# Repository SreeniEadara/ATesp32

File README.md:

# ATesp32

This is an ATmega32A replacement that uses the ESP32-S3.
Why? Because I bought ATmega32-based keyboard PCBs (the Discipline), love it and want to add wireless capabilities (BLE) and native USB.

I've made efforts to maintain the same number of GPIO, but there will be many differences you would encounter if trying to use this as an ATmega32A replacement. These would include logic levels, availability of analog pins, clock, etc.

Thank you to Adafruit for making the Feather and QtPy boards for the ESP32-S3!
I heavily referenced these in this design.
https://github.com/adafruit/Adafruit-Feather-ESP32-S3-PCB
https://github.com/adafruit/Adafruit-QT-Py-ESP32-S3-PCB/tree/main

Call me an Adafruit shill if you will, but you can support open hardware by purchasing from them.

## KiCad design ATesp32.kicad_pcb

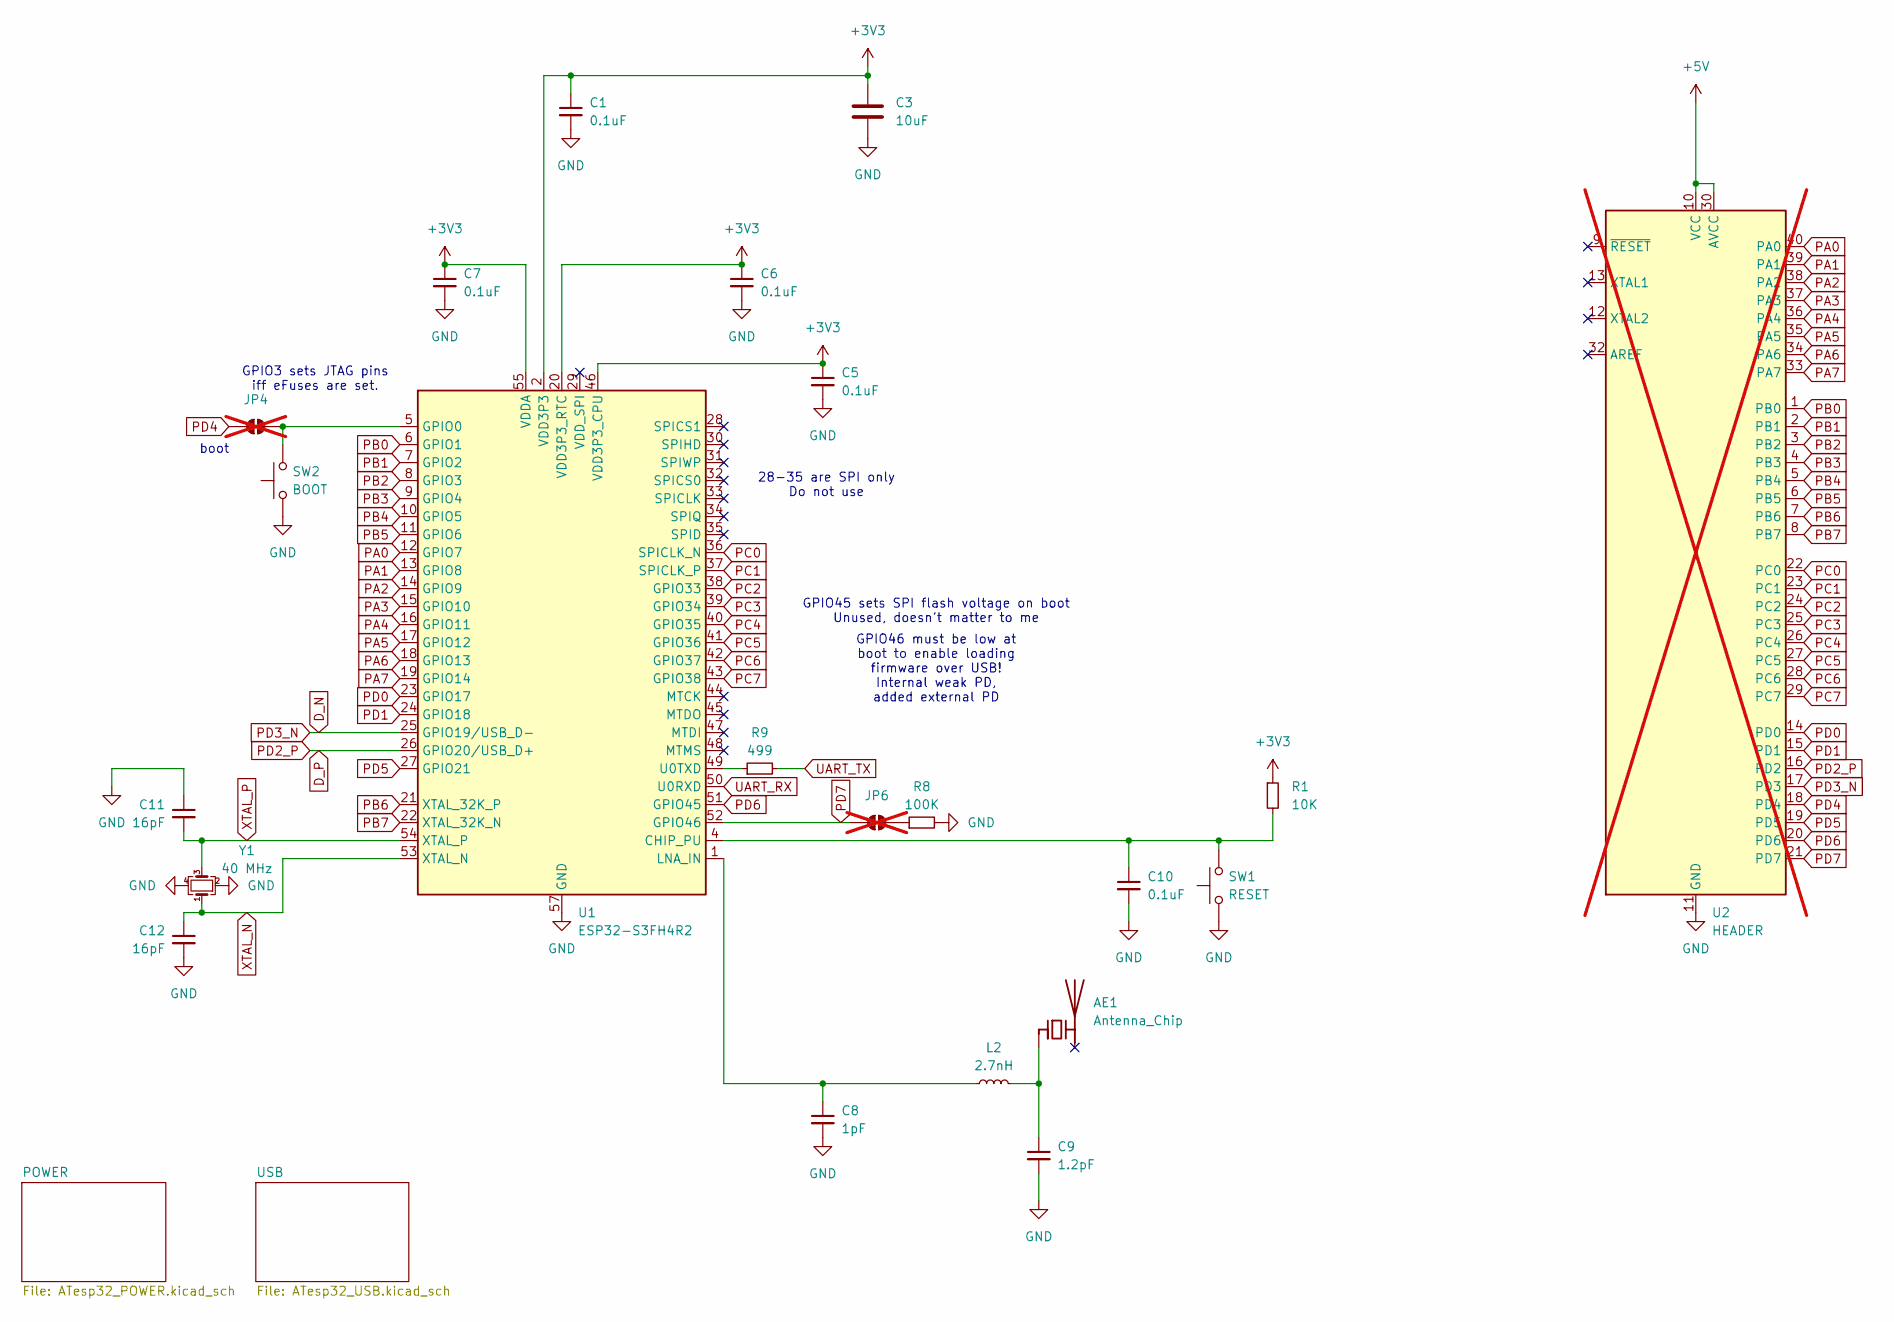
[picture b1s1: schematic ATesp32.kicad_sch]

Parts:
AE1: Antenna_Chip; Johanson_2450AT18x100; DigiKey 712-2450AT18B0100001ECT-ND
C1, C5, C6, C7, C10: 0.1uF; C_0402_1005Metric; LCSC C1525
C3: 10uF; C_0402_1005Metric; LCSC C315248
C8: 1pF; C_0402_1005Metric; DigiKey 1276-6609-1-ND
C9: 1.2pF; C_0402_1005Metric; DigiKey 1276-1654-1-ND
C11, C12: 16pF; C_0402_1005Metric; LCSC C541434
JP4, JP6: SolderJumper_2_Open; SolderJumper-2_P1.3mm_Open_RoundedPad1.0x1.5mm; not fitted
L2: 2.7nH; L_0402_1005Metric; LCSC C434826
R1: 10K; R_0402_1005Metric; LCSC C25744
R8: 100K; R_0402_1005Metric; LCSC C25741
R9: 499; R_0402_1005Metric; LCSC C4125
SW1: RESET; SW_Push_1P1T_NO_CK_KMR2; LCSC C221680
SW2: BOOT; SW_Push_1P1T_NO_CK_KMR2; LCSC C221680
U1: ESP32-S3FH4R2; QFN-56-1EP_7x7mm_P0.4mm_EP4x4mm; Mouser 356-ESP32-S3FH4R2
U2: HEADER; DIP-40_W15.24mm; not fitted
Y1: 40 MHz; Crystal_SMD_Abracon_ABM8G-4Pin_3.2x2.5mm; DigiKey 535-14086-1-ND

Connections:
+3V3: C1.1, C3.1, C5.1, C6.1, C7.1, R1.1, U1.2 (VDD3P3), U1.3 (VDD3P3), U1.20 (VDD3P3_RTC), U1.46 (VDD3P3_CPU), U1.55 (VDDA), U1.56 (VDDA); also elsewhere on the board
+5V: U2.10 (VCC), U2.30 (AVCC); also elsewhere on the board
D_N: U1.25 (GPIO19/USB_D-), U2.17 (PD3)
D_P: U1.26 (GPIO20/USB_D+), U2.16 (PD2)
GND: C1.2, C3.2, C5.2, C6.2, C7.2, C8.2, C9.2, C10.2, C11.1, C12.2, R8.2, SW1.1, SW2.1, U1.57 (GND), U2.11 (GND), U2.31 (GND), Y1.2, Y1.4; also elsewhere on the board
unnamed: AE1.1 (FEED), C9.1, L2.2
unnamed: JP4.2 (B), SW2.2, U1.5 (GPIO0)
unnamed: JP6.2 (B), R8.1
unnamed: C10.1, R1.2, SW1.2, U1.4 (CHIP_PU)
unnamed: C8.1, L2.1, U1.1 (LNA_IN)
unnamed: R9.1, U1.49 (U0TXD)
PA0: U1.12 (GPIO7), U2.40 (PA0)
PA1: U1.13 (GPIO8), U2.39 (PA1)
PA2: U1.14 (GPIO9), U2.38 (PA2)
PA3: U1.15 (GPIO10), U2.37 (PA3)
PA4: U1.16 (GPIO11), U2.36 (PA4)
PA5: U1.17 (GPIO12), U2.35 (PA5)
PA6: U1.18 (GPIO13), U2.34 (PA6)
PA7: U1.19 (GPIO14), U2.33 (PA7)
PB0: U1.6 (GPIO1), U2.1 (PB0)
PB1: U1.7 (GPIO2), U2.2 (PB1)
PB2: U1.8 (GPIO3), U2.3 (PB2)
PB3: U1.9 (GPIO4), U2.4 (PB3)
PB4: U1.10 (GPIO5), U2.5 (PB4)
PB5: U1.11 (GPIO6), U2.6 (PB5)
PB6: U1.21 (XTAL_32K_P), U2.7 (PB6)
PB7: U1.22 (XTAL_32K_N), U2.8 (PB7)
PC0: U1.36 (SPICLK_N), U2.22 (PC0)
PC1: U1.37 (SPICLK_P), U2.23 (PC1)
PC2: U1.38 (GPIO33), U2.24 (PC2)
PC3: U1.39 (GPIO34), U2.25 (PC3)
PC4: U1.40 (GPIO35), U2.26 (PC4)
PC5: U1.41 (GPIO36), U2.27 (PC5)
PC6: U1.42 (GPIO37), U2.28 (PC6)
PC7: U1.43 (GPIO38), U2.29 (PC7)
PD0: U1.23 (GPIO17), U2.14 (PD0)
PD1: U1.24 (GPIO18), U2.15 (PD1)
PD4: JP4.1 (A), U2.18 (PD4)
PD5: U1.27 (GPIO21), U2.19 (PD5)
PD6: U1.51 (GPIO45), U2.20 (PD6)
PD7: JP6.1 (A), U1.52 (GPIO46), U2.21 (PD7)
UART_RX: U1.50 (U0RXD); also elsewhere on the board
UART_TX: R9.2; also elsewhere on the board
XTAL_N: C12.1, U1.53 (XTAL_N), Y1.1
XTAL_P: C11.2, U1.54 (XTAL_P), Y1.3

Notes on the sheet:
GPIO45 sets SPI flash voltage on boot Unused, doesn't matter to me
boot
28-35 are SPI only Do not use
GPIO3 sets JTAG pins iff eFuses are set.
GPIO46 must be low at boot to enable loading firmware over USB! Internal weak PD, added external PD

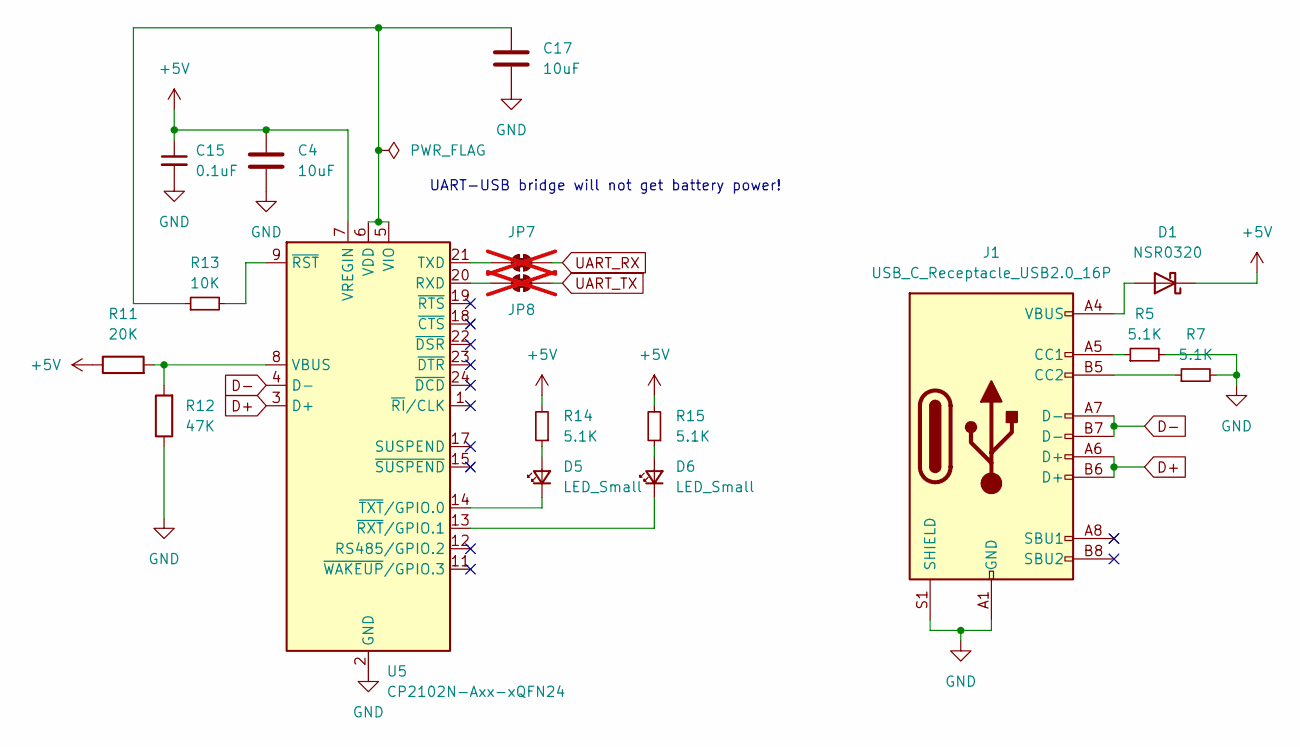
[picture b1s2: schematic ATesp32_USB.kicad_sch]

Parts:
C4, C17: 10uF; C_0402_1005Metric; LCSC C315248
C15: 0.1uF; C_0402_1005Metric; LCSC C1525
D1: NSR0320; D_SOD-323; LCSC C48192
D5, D6: LED_Small; LED_0402_1005Metric; LCSC C510300
J1: USB_C_Receptacle_USB2.0_16P; USB_C_Receptacle_GCT_USB4105-xx-A_16P_TopMnt_Horizontal; LCSC C2988369
JP7, JP8: SolderJumper_2_Bridged; SolderJumper-2_P1.3mm_Bridged_RoundedPad1.0x1.5mm; not fitted
R5, R7, R14, R15: 5.1K; R_0402_1005Metric; LCSC C25905
R11: 20K; R_0402_1005Metric; LCSC C25765
R12: 47K; R_0402_1005Metric; LCSC C25792
R13: 10K; R_0402_1005Metric; LCSC C25744
U5: CP2102N-Axx-xQFN24; QFN-24-1EP_4x4mm_P0.5mm_EP2.6x2.6mm; LCSC C969151

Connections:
+5V: C4.1, C15.1, D1.1 (K), R11.1, R14.2, R15.2, U5.7 (VREGIN); also elsewhere on the board
D+: J1.A6 (D+), J1.B6 (D+), U5.3 (D+)
D-: J1.A7 (D-), J1.B7 (D-), U5.4 (D-)
GND: C4.2, C15.2, C17.2, J1.A1 (GND), J1.A12 (GND), J1.B1 (GND), J1.B12 (GND), J1.S1 (SHIELD), R5.2, R7.2, R12.1, U5.2 (GND), U5.25 (GND); also elsewhere on the board
unnamed: D1.2 (A), J1.A4 (VBUS), J1.A9 (VBUS), J1.B4 (VBUS), J1.B9 (VBUS)
unnamed: D5.2 (A), R14.1
unnamed: D5.1 (K), U5.14 (~TXT/GPIO.0)
unnamed: D6.2 (A), R15.1
unnamed: D6.1 (K), U5.13 (~RXT/GPIO.1)
unnamed: J1.A5 (CC1), R5.1
unnamed: J1.B5 (CC2), R7.1
unnamed: JP7.1 (A), U5.21 (TXD)
unnamed: JP8.1 (A), U5.20 (RXD)
unnamed: R11.2, R12.2, U5.8 (VBUS)
unnamed: C17.1, R13.1, U5.5 (VIO), U5.6 (VDD)
unnamed: R13.2, U5.9 (~RST)
UART_RX: JP7.2 (B); also elsewhere on the board
UART_TX: JP8.2 (B); also elsewhere on the board

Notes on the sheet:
UART-USB bridge will not get battery power!

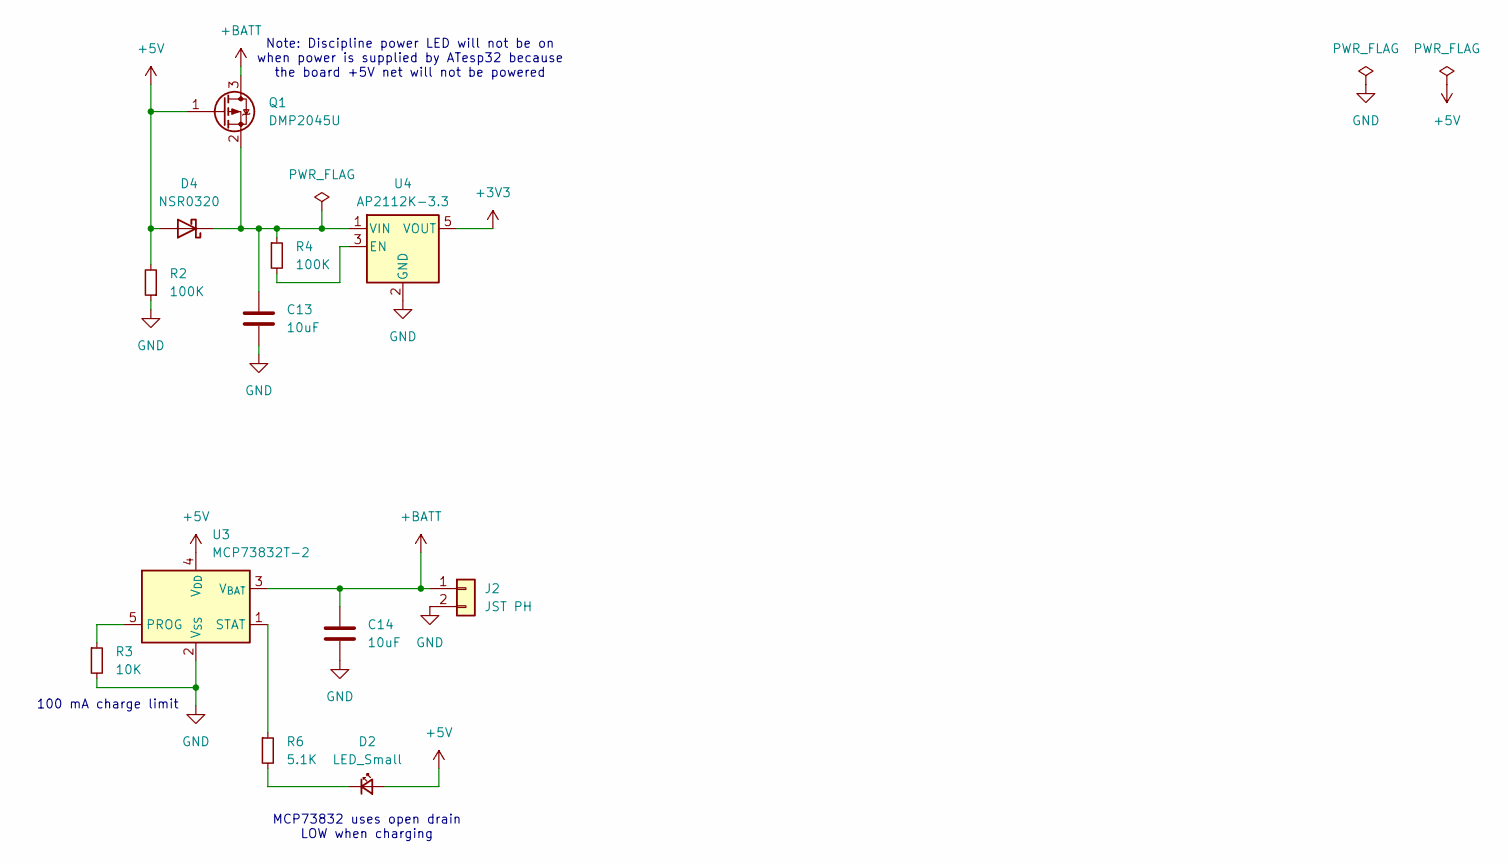
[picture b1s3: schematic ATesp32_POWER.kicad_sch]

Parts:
C13, C14: 10uF; C_0402_1005Metric; LCSC C315248
D2: LED_Small; LED_0402_1005Metric; LCSC C510300
D4: NSR0320; D_SOD-323; LCSC C48192
J2: JST PH; JST_PH_S2B-PH-SM4-TB_1x02-1MP_P2.00mm_Horizontal; LCSC C295747
Q1: DMP2045U; SOT-23; LCSC C459541
R2, R4: 100K; R_0402_1005Metric; LCSC C25741
R3: 10K; R_0402_1005Metric; LCSC C25744
R6: 5.1K; R_0402_1005Metric; LCSC C25905
U3: MCP73832T-2; SOT-23-5; LCSC C38066
U4: AP2112K-3.3; SOT-23-5; LCSC C51118

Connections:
+3V3: U4.5 (VOUT); also elsewhere on the board
+5V: D2.2 (A), D4.2 (A), Q1.1 (G), R2.2, U3.4 (V_{DD}); also elsewhere on the board
+BATT: C14.1, J2.1, Q1.3 (D), U3.3 (V_{BAT})
GND: C13.2, C14.2, J2.2, R2.1, R3.2, U3.2 (V_{SS}), U4.2 (GND); also elsewhere on the board
unnamed: D2.1 (K), R6.2
unnamed: C13.1, D4.1 (K), Q1.2 (S), R4.1, U4.1 (VIN)
unnamed: R3.1, U3.5 (PROG)
unnamed: R6.1, U3.1 (STAT)
unnamed: R4.2, U4.3 (EN)

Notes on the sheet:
100 mA charge limit
Note: Discipline power LED will not be on when power is supplied by ATesp32 because the board +5V net will not be powered
MCP73832 uses open drain LOW when charging

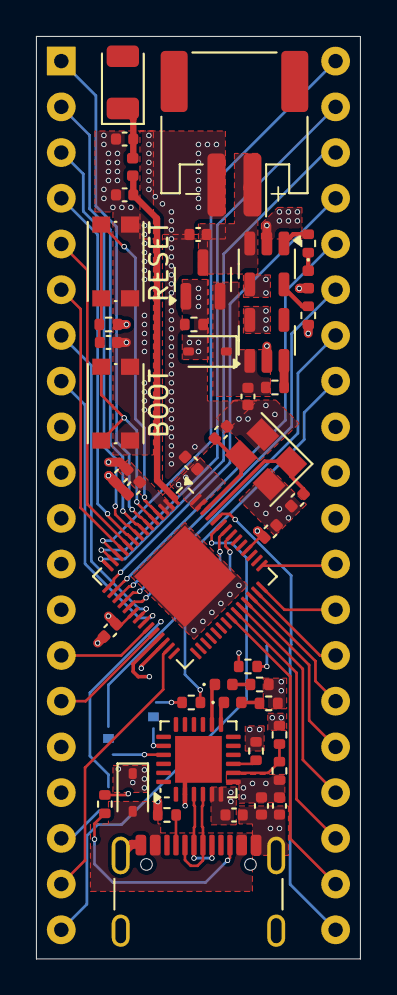
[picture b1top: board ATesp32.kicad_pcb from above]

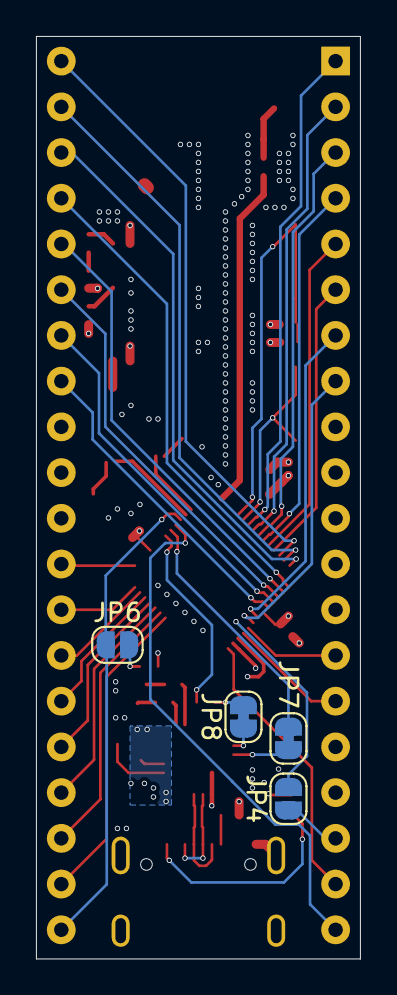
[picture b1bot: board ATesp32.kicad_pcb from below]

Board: 4 copper layers, 18.0 x 51.2 mm, 51 parts (4 on the bottom side), 65 nets.

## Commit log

2024-11-10 Adding ATesp32 schematic. In development
2024-11-10 Adding project README
2024-11-10 Added USB-UART bridge for programming
2024-11-10 first pass at footprint assignment
2024-11-10 remove misc superfluous components
2024-11-10 fix gitignore
2024-11-11 first pass at component placement
2024-11-11 centered headers and USB-C. Set grid and drill origins
2024-11-12 Finished layout, need to fix silk
2024-11-12 fix USB routing
2024-11-13 fix pours
2024-11-14 Better fencing near antenna trace
2024-11-14 adjust 3v3 pour
2024-11-14 cleanup
2024-11-16 fix silk
2024-11-16 move crystal farther from chip
2024-11-16 critical error - changed to correct mosfet pin numbers
2024-11-16 satisfy DRC and ERC
2024-11-16 antenna was backwards
2024-11-16 small layout optimization
2024-11-16 fix bug - correct use of open drain status signal of lipo charger
2024-11-16 spec components for JLC
2024-11-16 Generate production files. More clear part names for ESP and LiPo charger
2024-11-17 generated manf files. Too damn expensive, adjusting min track and holes
2024-11-17 change project settings
2024-11-24 Add some Mouser PNs
2024-11-24 update manf outputs
2024-12-09 USB-UART Bridge LEDs had wrong orientation. Fixed
2025-01-07 LEDs were persistently on. Change to active low config see CP2102N datasheet fig 4.3
